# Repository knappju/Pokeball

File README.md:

# __Pokeball__
## __Project Info__

__Created:__                        December 3, 2021
__Project Version:__                v 0.0.0.5  
__Stable Branch:__                  master

### __Code__
* __IDE:__ MPLAB X IDE v5.45

__Last Release Date:__              January 1, 2022  
__Last Stable Release:__            v 0.0.0.4 

### __ECAD__
* __CAD:__ KiCAD v5.1.10

__Last Release Date:__              January 1, 2022  
__Last Stable Release:__            v 0.0.0.2

## Versioning

For the versions available, see the [tags on this repository](https://github.com/knappju/Pokeball/commits/master). 
## Authors

* **Justin Knapp** - *Circuit Design, PCB Design, Code, Mechanical Design*

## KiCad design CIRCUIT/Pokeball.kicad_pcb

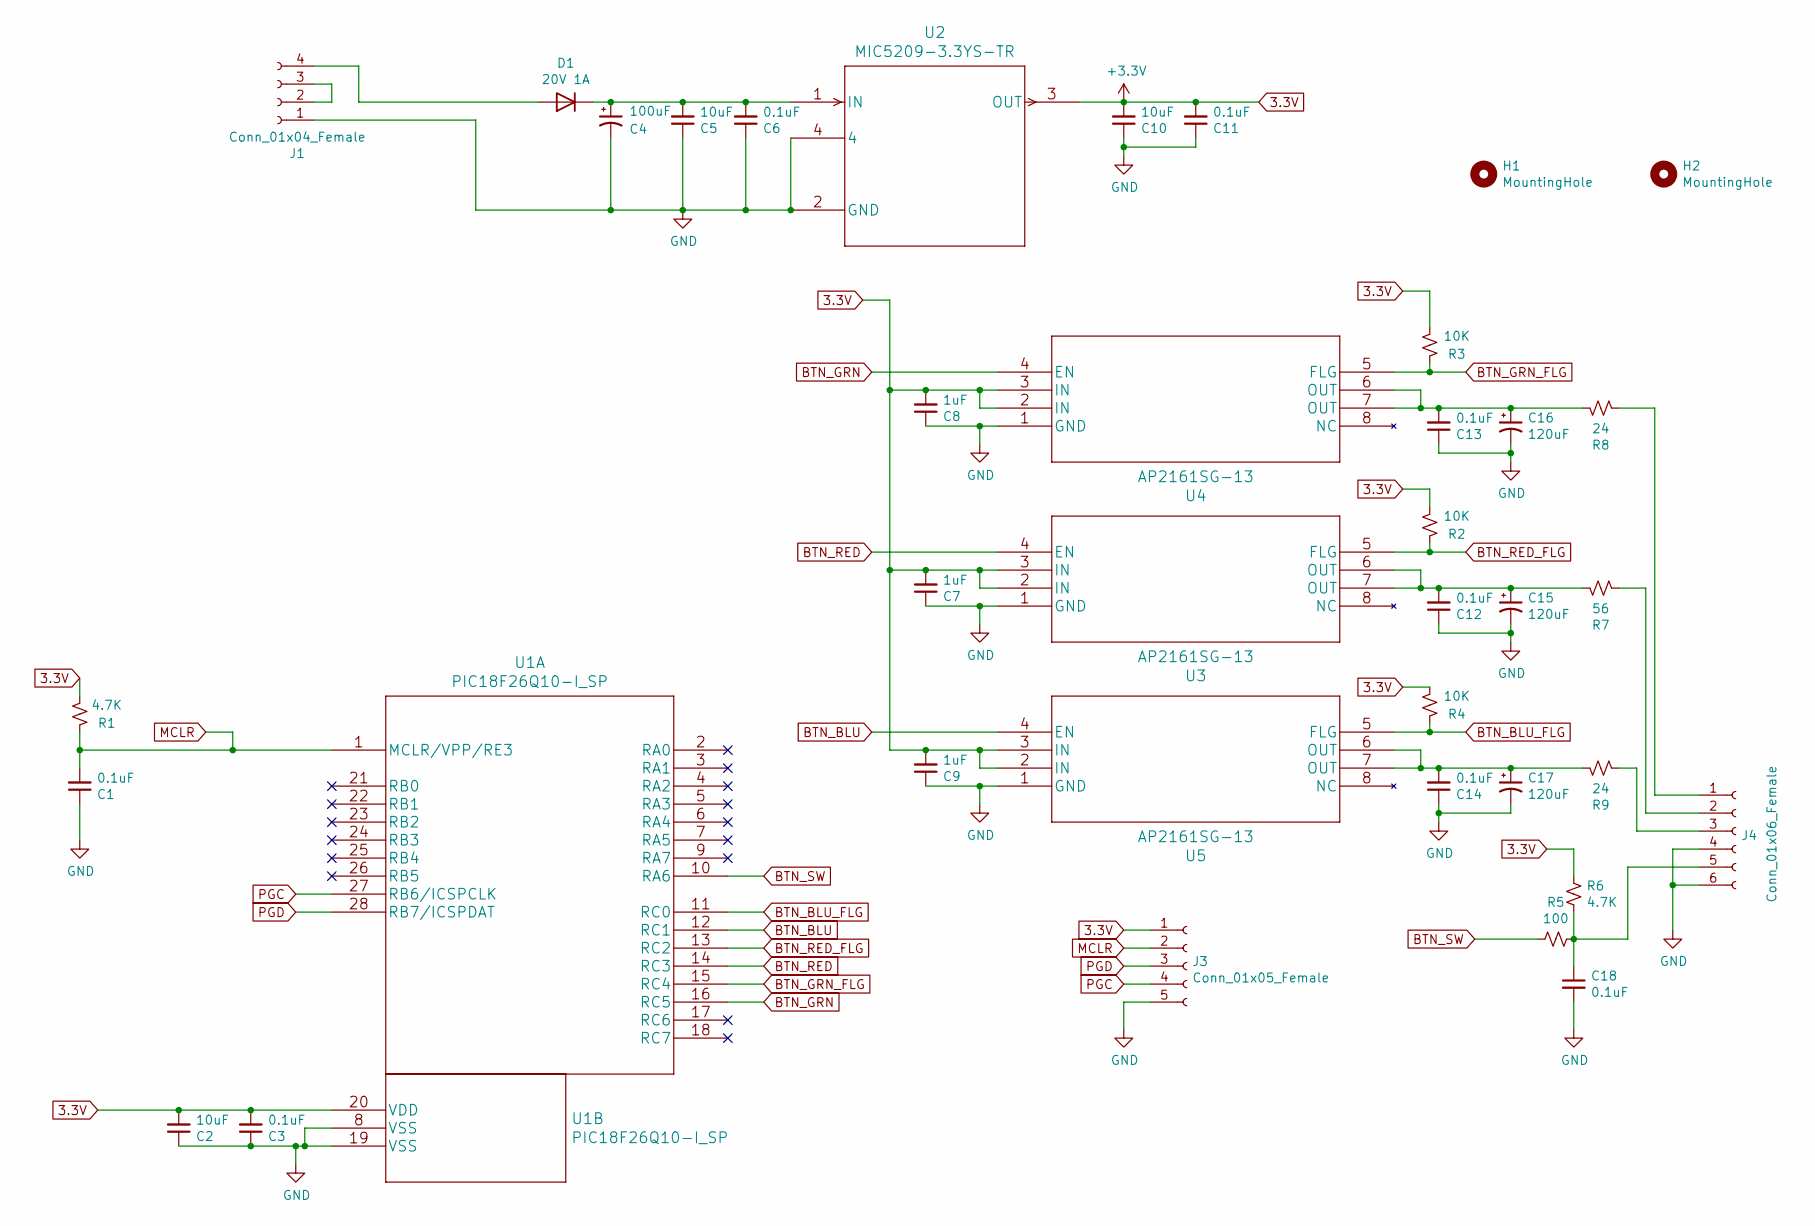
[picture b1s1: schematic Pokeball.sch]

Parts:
C1, C3, C6, C11, C12, C13, C14, C18: 0.1uF; C_0805_2012Metric_Pad1.18x1.45mm_HandSolder
C2, C5, C10: 10uF; C_0805_2012Metric_Pad1.18x1.45mm_HandSolder
C4: 100uF; CP_Radial_D5.0mm_P2.50mm
C7, C8, C9: 1uF; C_0805_2012Metric_Pad1.18x1.45mm_HandSolder
C15, C16, C17: 120uF; CP_Radial_D5.0mm_P2.50mm
D1: 20V 1A; D_SOD-123
H1, H2: MountingHole; MountingHole_2.2mm_M2_DIN965
J1: Conn_01x04_Female; PinHeader_1x04_P2.54mm_Vertical
J3: Conn_01x05_Female; PinHeader_1x05_P2.00mm_Vertical
J4: Conn_01x06_Female; PinHeader_1x06_P2.00mm_Vertical
R1, R6: 4.7K; R_0805_2012Metric_Pad1.20x1.40mm_HandSolder
R2, R3, R4: 10K; R_0805_2012Metric_Pad1.20x1.40mm_HandSolder
R5: 100; R_0805_2012Metric_Pad1.20x1.40mm_HandSolder
R7: 56; R_0805_2012Metric_Pad1.20x1.40mm_HandSolder
R8, R9: 24; R_0805_2012Metric_Pad1.20x1.40mm_HandSolder
U1: PIC18F26Q10-I_SP; PIC18F26Q10-I&slash_SP
U2: MIC5209-3.3YS-TR
U3, U4, U5: AP2161SG-13

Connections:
3.3V: C2.2, C3.2, C7.2, C8.2, C9.2, C10.2, C11.2, J3.1, R1.2, R2.2, R3.2, R4.2, R6.2, U1.20 (VDD), U2.3 (OUT), U3.2 (IN), U3.3 (IN), U4.2 (IN), U4.3 (IN), U5.2 (IN), U5.3 (IN)
BTN_BLU: U1.12 (RC1), U5.4 (EN)
BTN_BLU_FLG: R4.1, U1.11 (RC0), U5.5 (FLG)
BTN_GRN: U1.16 (RC5), U4.4 (EN)
BTN_GRN_FLG: R3.1, U1.15 (RC4), U4.5 (FLG)
BTN_RED: U1.14 (RC3), U3.4 (EN)
BTN_RED_FLG: R2.1, U1.13 (RC2), U3.5 (FLG)
BTN_SW: R5.2, U1.10 (RA6)
GND: C1.1, C2.1, C3.1, C4.2, C5.1, C6.1, C7.1, C8.1, C9.1, C10.1, C11.1, C12.1, C13.1, C14.1, C15.2, C16.2, C17.2, C18.2, J1.1, J3.5, J4.4, J4.6, U1.8 (VSS), U1.19 (VSS), U2.2 (GND), U2.4, U3.1 (GND), U4.1 (GND), U5.1 (GND)
MCLR: C1.2, J3.2, R1.1, U1.1 (MCLR/VPP/RE3)
unnamed: C4.1, C5.2, C6.2, D1.1 (K), U2.1 (IN)
unnamed: C12.2, C15.1, R7.2, U3.6 (OUT), U3.7 (OUT)
unnamed: C13.2, C16.1, R8.2, U4.6 (OUT), U4.7 (OUT)
unnamed: C14.2, C17.1, R9.2, U5.6 (OUT), U5.7 (OUT)
unnamed: C18.1, J4.5, R5.1, R6.1
unnamed: D1.2 (A), J1.4
unnamed: J1.2, J1.3
unnamed: J4.1, R8.1
unnamed: J4.2, R7.1
unnamed: J4.3, R9.1
PGC: J3.4, U1.27 (RB6/ICSPCLK)
PGD: J3.3, U1.28 (RB7/ICSPDAT)

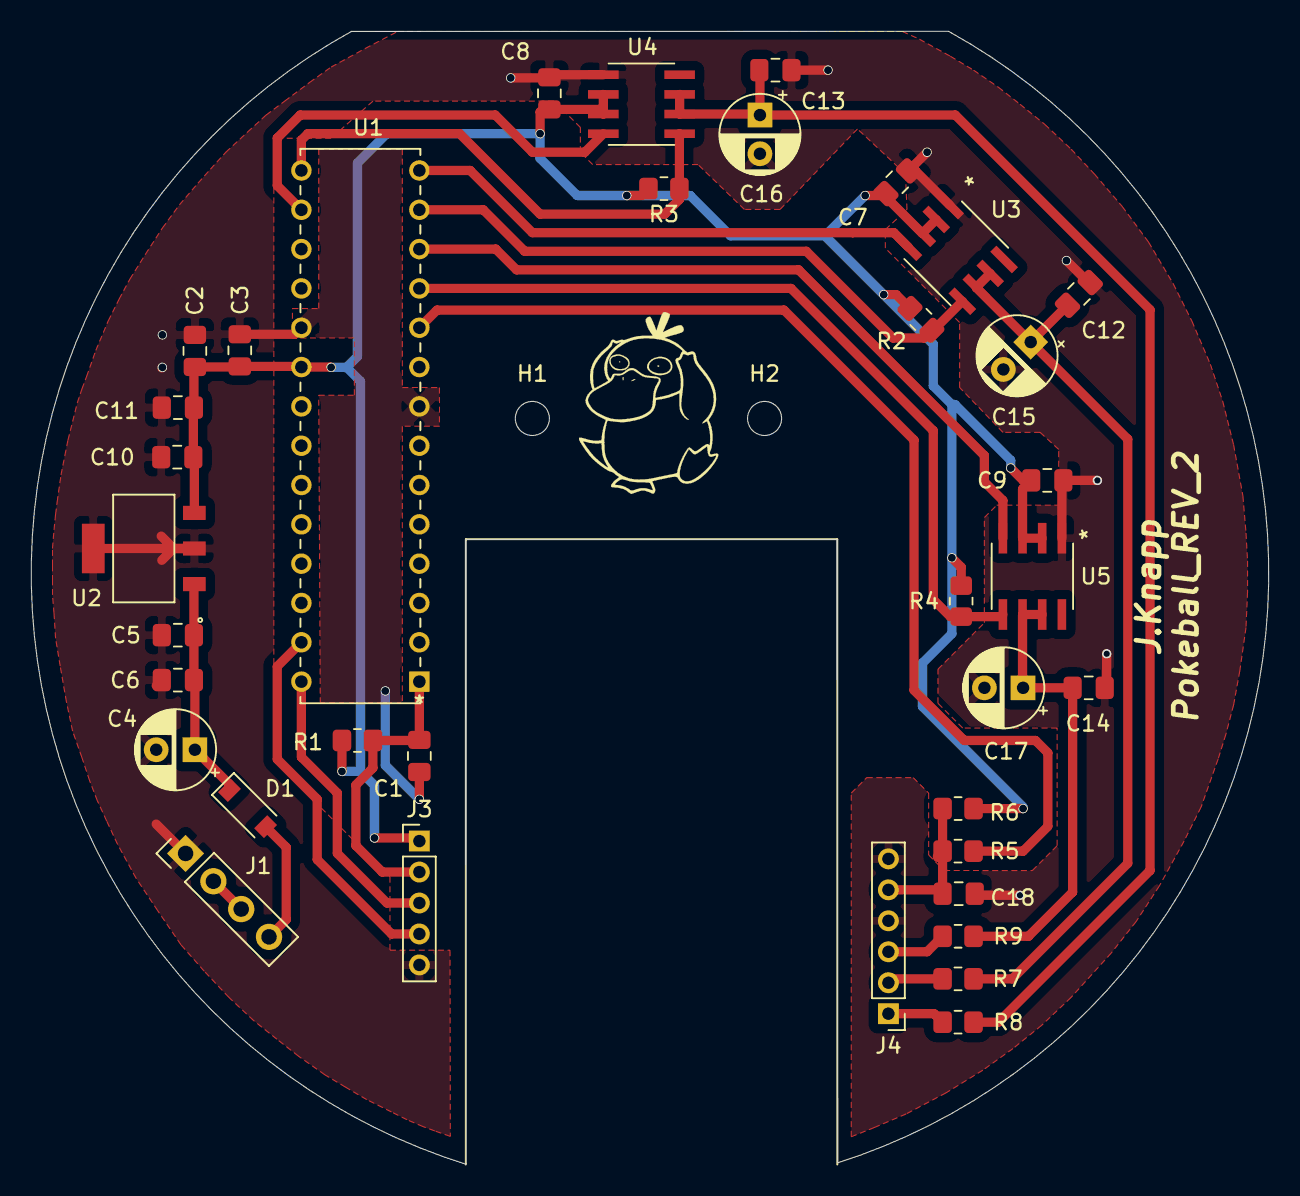
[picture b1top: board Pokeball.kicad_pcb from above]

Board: 2 copper layers, 79.9 x 73.2 mm, 38 parts (0 on the bottom side), 22 nets.

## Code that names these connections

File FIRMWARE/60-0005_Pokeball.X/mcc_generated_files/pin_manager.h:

/**
  @Generated Pin Manager Header File

  @Company:
    Microchip Technology Inc.

  @File Name:
    pin_manager.h

  @Summary:
    This is the Pin Manager file generated using PIC10 / PIC12 / PIC16 / PIC18 MCUs

  @Description
    This header file provides APIs for driver for .
    Generation Information :
        Product Revision  :  PIC10 / PIC12 / PIC16 / PIC18 MCUs - 1.81.7
        Device            :  PIC18F26Q10
        Driver Version    :  2.11
    The generated drivers are tested against the following:
        Compiler          :  XC8 2.31 and above
        MPLAB 	          :  MPLAB X 5.45	
*/

/*
    (c) 2018 Microchip Technology Inc. and its subsidiaries. 
    
    Subject to your compliance with these terms, you may use Microchip software and any 
    derivatives exclusively with Microchip products. It is your responsibility to comply with third party 
    license terms applicable to your use of third party software (including open source software) that 
    may accompany Microchip software.
    
    THIS SOFTWARE IS SUPPLIED BY MICROCHIP "AS IS". NO WARRANTIES, WHETHER 
    EXPRESS, IMPLIED OR STATUTORY, APPLY TO THIS SOFTWARE, INCLUDING ANY 
    IMPLIED WARRANTIES OF NON-INFRINGEMENT, MERCHANTABILITY, AND FITNESS 
    FOR A PARTICULAR PURPOSE.
    
    IN NO EVENT WILL MICROCHIP BE LIABLE FOR ANY INDIRECT, SPECIAL, PUNITIVE, 
    INCIDENTAL OR CONSEQUENTIAL LOSS, DAMAGE, COST OR EXPENSE OF ANY KIND 
    WHATSOEVER RELATED TO THE SOFTWARE, HOWEVER CAUSED, EVEN IF MICROCHIP 
    HAS BEEN ADVISED OF THE POSSIBILITY OR THE DAMAGES ARE FORESEEABLE. TO 
    THE FULLEST EXTENT ALLOWED BY LAW, MICROCHIP'S TOTAL LIABILITY ON ALL 
    CLAIMS IN ANY WAY RELATED TO THIS SOFTWARE WILL NOT EXCEED THE AMOUNT 
    OF FEES, IF ANY, THAT YOU HAVE PAID DIRECTLY TO MICROCHIP FOR THIS 
    SOFTWARE.
*/

#ifndef PIN_MANAGER_H
#define PIN_MANAGER_H

/**
  Section: Included Files
*/

#include <xc.h>

#define INPUT   1
#define OUTPUT  0

#define HIGH    1
#define LOW     0

#define ANALOG      1
#define DIGITAL     0

#define PULL_UP_ENABLED      1
#define PULL_UP_DISABLED     0

// get/set CB aliases
#define CB_TRIS                 TRISAbits.TRISA6
#define CB_LAT                  LATAbits.LATA6
#define CB_PORT                 PORTAbits.RA6
#define CB_WPU                  WPUAbits.WPUA6
#define CB_OD                   ODCONAbits.ODCA6
#define CB_ANS                  ANSELAbits.ANSELA6
#define CB_SetHigh()            do { LATAbits.LATA6 = 1; } while(0)
#define CB_SetLow()             do { LATAbits.LATA6 = 0; } while(0)
#define CB_Toggle()             do { LATAbits.LATA6 = ~LATAbits.LATA6; } while(0)
#define CB_GetValue()           PORTAbits.RA6
#define CB_SetDigitalInput()    do { TRISAbits.TRISA6 = 1; } while(0)
#define CB_SetDigitalOutput()   do { TRISAbits.TRISA6 = 0; } while(0)
#define CB_SetPullup()          do { WPUAbits.WPUA6 = 1; } while(0)
#define CB_ResetPullup()        do { WPUAbits.WPUA6 = 0; } while(0)
#define CB_SetPushPull()        do { ODCONAbits.ODCA6 = 0; } while(0)
#define CB_SetOpenDrain()       do { ODCONAbits.ODCA6 = 1; } while(0)
#define CB_SetAnalogMode()      do { ANSELAbits.ANSELA6 = 1; } while(0)
#define CB_SetDigitalMode()     do { ANSELAbits.ANSELA6 = 0; } while(0)

// get/set RC1 procedures
#define RC1_SetHigh()            do { LATCbits.LATC1 = 1; } while(0)
#define RC1_SetLow()             do { LATCbits.LATC1 = 0; } while(0)
#define RC1_Toggle()             do { LATCbits.LATC1 = ~LATCbits.LATC1; } while(0)
#define RC1_GetValue()              PORTCbits.RC1
#define RC1_SetDigitalInput()    do { TRISCbits.TRISC1 = 1; } while(0)
#define RC1_SetDigitalOutput()   do { TRISCbits.TRISC1 = 0; } while(0)
#define RC1_SetPullup()             do { WPUCbits.WPUC1 = 1; } while(0)
#define RC1_ResetPullup()           do { WPUCbits.WPUC1 = 0; } while(0)
#define RC1_SetAnalogMode()         do { ANSELCbits.ANSELC1 = 1; } while(0)
#define RC1_SetDigitalMode()        do { ANSELCbits.ANSELC1 = 0; } while(0)

// get/set RC3 procedures
#define RC3_SetHigh()            do { LATCbits.LATC3 = 1; } while(0)
#define RC3_SetLow()             do { LATCbits.LATC3 = 0; } while(0)
#define RC3_Toggle()             do { LATCbits.LATC3 = ~LATCbits.LATC3; } while(0)
#define RC3_GetValue()              PORTCbits.RC3
#define RC3_SetDigitalInput()    do { TRISCbits.TRISC3 = 1; } while(0)
#define RC3_SetDigitalOutput()   do { TRISCbits.TRISC3 = 0; } while(0)
#define RC3_SetPullup()             do { WPUCbits.WPUC3 = 1; } while(0)
#define RC3_ResetPullup()           do { WPUCbits.WPUC3 = 0; } while(0)
#define RC3_SetAnalogMode()         do { ANSELCbits.ANSELC3 = 1; } while(0)
#define RC3_SetDigitalMode()        do { ANSELCbits.ANSELC3 = 0; } while(0)

// get/set RC5 procedures
#define RC5_SetHigh()            do { LATCbits.LATC5 = 1; } while(0)
#define RC5_SetLow()             do { LATCbits.LATC5 = 0; } while(0)
#define RC5_Toggle()             do { LATCbits.LATC5 = ~LATCbits.LATC5; } while(0)
#define RC5_GetValue()              PORTCbits.RC5
#define RC5_SetDigitalInput()    do { TRISCbits.TRISC5 = 1; } while(0)
#define RC5_SetDigitalOutput()   do { TRISCbits.TRISC5 = 0; } while(0)
#define RC5_SetPullup()             do { WPUCbits.WPUC5 = 1; } while(0)
#define RC5_ResetPullup()           do { WPUCbits.WPUC5 = 0; } while(0)
#define RC5_SetAnalogMode()         do { ANSELCbits.ANSELC5 = 1; } while(0)
#define RC5_SetDigitalMode()        do { ANSELCbits.ANSELC5 = 0; } while(0)

/**
   @Param
    none
   @Returns
    none
   @Description
    GPIO and peripheral I/O initialization
   @Example
    PIN_MANAGER_Initialize();
 */
void PIN_MANAGER_Initialize (void);

/**
 * @Param
    none
 * @Returns
    none
 * @Description
    Interrupt on Change Handling routine
 * @Example
    PIN_MANAGER_IOC();
 */
void PIN_MANAGER_IOC(void);



#endif // PIN_MANAGER_H
/**
 End of File
*/

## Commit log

2021-12-03 v 0.0.0.1 - Create GitHub Repo
2021-12-21 v 0.0.0.2 - Init PWM for RGB button
2021-12-21 v 0.0.0.3 - Structure for color added. Validation of color mixing with PWM.
2021-12-27 v 0.0.0.4 - Adding debounce button code. Seperate app.c into a rgbButton.h and .c
2022-01-02 v 0.0.0.5 - Restructure project. Include all pcb and circuit files.
2022-01-24 v 0.0.0.6 - Include more pokeball like features.

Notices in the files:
parts and their libraries:
Copyright 2021 Accelerated Designs. All rights reserved.
